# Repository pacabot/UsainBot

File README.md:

# UsainBot

Robot suiveur de ligne de l'équipe **Pacabot**, conçu pour l'épreuve **Formule 1** du
Tournoi National de Robotique Sumo (règlement v2.11, 2025).

Course de vitesse contre la montre sur circuit fermé : ligne noire de 19 mm sur bâche
blanche, rayon de virage minimum de 200 mm, lignes droites jusqu'à 6 m. Trois phases de
qualification, de difficulté croissante — Q3 piste nue, Q2 avec un cube de 100 mm à
éviter sans contact, Q1 avec en plus un virage à gauche escamoté et un mur de 100 mm de
haut placé à 150 mm à gauche de l'axe de la piste absente.

## Organisation

```
electronics/      projet KiCad — schéma, PCB, table de bibliothèques
  kicad-lib/      empreintes et modèles 3D propres au projet
firmware/         à venir : configuration STM32CubeMX du H723ZGT6, puis le code
mechanics/        sources FreeCAD du châssis, des supports et de la carte
documentation/    document d'architecture
rules/            règlement de l'épreuve
```

Les bibliothèques sont référencées en `${KIPRJMOD}/kicad-lib/…` : le dépôt se clone et
s'ouvre tel quel, sans chemin absolu ni variable d'environnement à déclarer.

Le projet s'ouvre avec **KiCad 10.0** stable. Le routage se fait avec un fork 10.99
(autorouteur) qui enregistre la carte dans un format que 10.0 refuse : après chaque
enregistrement depuis le fork, ramener la carte au format 10.0 avant de commiter.

```sh
cd electronics && python3 tools/to_kicad10.py UsainBot.kicad_pcb
```

## Architecture

Le document de conception — choix du microcontrôleur, schémas blocs, implantation,
élévations, affectation des broches, nomenclature JLCPCB et revue de conception en
trente-sept points — est ici (rédigé avant le passage au LQFP144 et au BPV10NF : le
schéma `electronics/UsainBot.pdf` fait foi là où ils divergent) :

**[`documentation/architecture-usainbot.html`](documentation/architecture-usainbot.html)**

| Fonction | Choix | JLCPCB |
|---|---|---|
| Microcontrôleur | STM32H723ZGT6, Cortex-M7 550 MHz, LQFP144 | `C730146` |
| Capteur de ligne | 12 × ITR8307/S17, pas 10 mm, émetteurs pulsés | `C81632` |
| Télémétrie | 3 × OPV302 + BPV10NF, détection synchrone | pose manuelle |
| Inertie | LSM6DSO, 6 axes, SPI | `C2655100` |
| Puissance moteurs | 2 × DRV8874, 6 A crête, retour de courant | `C1855818` |
| Motorisation | 2 × Faulhaber 1524T006SR + codeur IE2-1024 + réducteur 15/10 3,33:1 | hors carte |
| Charge | BQ25887, 2S élévateur depuis USB-C, équilibrage | `C2761614` |
| Alimentation | Pack 2S commun sur AMASS MR30, bus 5,0–7,3 V, buck 3,3 V | `C3200405` |
| Turbine | EDF 27 mm, ESC EMAX Bullet 12A monté debout | hors carte |

## Géométrie

La garde au sol vaut `rayon de roue − hauteur de l'axe moteur au-dessus du dessous de
carte`. Les roues JSumo JS4311 font 43 mm ; l'équerre usinée et trois cales de 1,6 mm
tirées du panneau de la carte placent l'axe à 16,50 mm au-dessus du dessous de carte, ce
qui donne **5,00 mm de garde**, dans la plage utile de l'ITR8307. Toutes les cotes
dérivent de `electronics/kicad-lib/faulhaber_geom.py` (détail dans
`electronics/kicad-lib/README.md`).

## Points ouverts

- **Pack commun 2S.** Cellules, capacité, chimie et protection générale à arrêter ; la
  recharge BQ25887 reste inhibée jusqu'à configuration et validation du firmware.
- **Montage de l'ESC.** L'empreinte `EMAX_Bullet_12A_Vertical_3Pin_PROTOTYPE` est tirée
  de photographies : mesurer pads, épaisseur et continuités de masse sur l'ESC réel avant
  fabrication.

- **Départ par télémètre.** Le chapitre 2 du règlement énumère trois moyens de départ —
  interrupteur, bouton poussoir, jack — et cette liste se lit comme limitative. Question à
  poser aux organisateurs ; un bouton physique conforme est conservé en secours.
- **Porteuse de la télémétrie.** À choisir hors de la bande de scintillement des
  éclairages et à l'écart des 38 kHz des barrières de chronométrage, avec un codage propre
  au robot pour la réjection par corrélation. À caler sur plaque d'essai. Rester à 12 mA :
  monter en fréquence pour débloquer les 48 mA de l'OPV302 ne change pas la puissance
  moyenne, donc pas la portée — les deux régimes donnent 1,26 mW. Le seul levier de portée
  est la surface du récepteur.
- **Inclinaison des diodes.** 4° vers le haut, soudées à plat sur la carte. Le rayon bas du
  faisceau monte alors de 35 mm par mètre et n'atteint jamais la bâche, mais le centre passe
  au-dessus d'un cube de 100 mm au-delà d'environ un mètre.
- **Approvisionnement.** OPV302 et BPV10NF ne sont probablement pas dans la bibliothèque
  JLCPCB : pose manuelle des six composants de la languette à prévoir.
- **Poussée de la turbine.** À mesurer sous 6,4 V et non sous les 8,4 V pour lesquels les
  ensembles ESC et brushless du commerce sont calibrés.

## Contenu tiers

- `rules/Reglement-Formule-1-v2.11.pdf` — règlement rédigé par Frédéric Giamarchi et
  Jean-Roch Vaillé pour le Tournoi National de Robotique Sumo. Publié sur
  [robot-sumo.fr](https://robot-sumo.fr), reproduit ici pour le confort de travail de
  l'équipe. Tous droits réservés à leurs auteurs.
- `electronics/kicad-lib/3d/vendor/*.stp` — modèles Faulhaber du moteur 1524 et du
  réducteur 15/10. Provenance dans `electronics/kicad-lib/3d/vendor/README.md`.

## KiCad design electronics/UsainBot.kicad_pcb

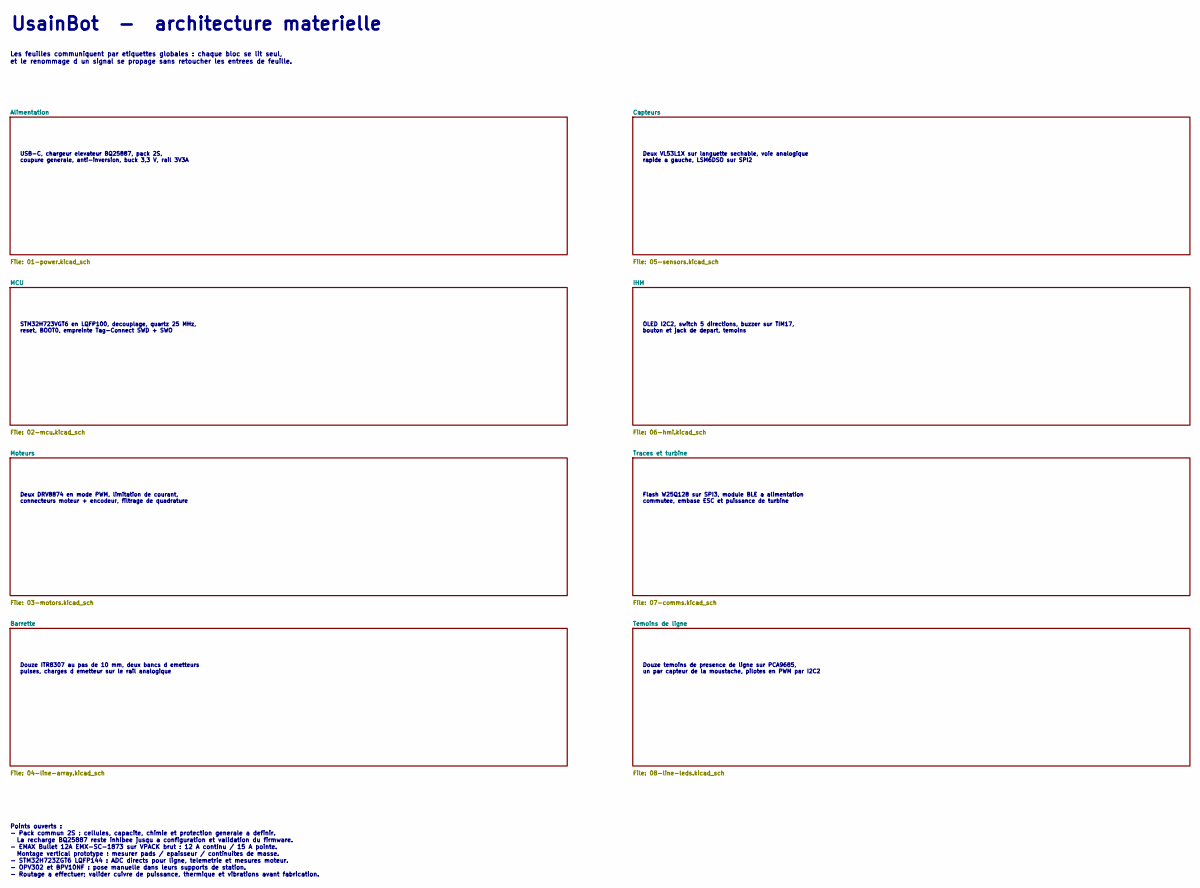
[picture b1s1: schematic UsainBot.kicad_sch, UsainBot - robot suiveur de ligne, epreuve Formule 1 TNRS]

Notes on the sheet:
USB-C, chargeur elevateur BQ25887, pack 2S, coupure generale, anti-inversion, buck 3,3 V, rail 3V3A
Flash W25Q128 sur SPI3, module BLE a alimentation commutee, embase ESC et puissance de turbine
Douze ITR8307 au pas de 10 mm, deux bancs d emetteurs pulses, charges d emetteur sur le rail analogique
Douze temoins de presence de ligne sur PCA9685, un par capteur de la moustache, pilotes en PWM par I2C2
Les feuilles communiquent par etiquettes globales : chaque bloc se lit seul, et le renommage d un signal se propage sans retoucher les entrees de feuille.
Deux VL53L1X sur languette sechable, voie analogique rapide a gauche, LSM6DSO sur SPI2
OLED I2C2, switch 5 directions, buzzer sur TIM17, bouton et jack de depart, temoins
Deux DRV8874 en mode PWM, limitation de courant, connecteurs moteur + encodeur, filtrage de quadrature
STM32H723VGT6 en LQFP100, decouplage, quartz 25 MHz, reset, BOOT0, empreinte Tag-Connect SWD + SWO
Points ouverts : - Pack commun 2S : cellules, capacite, chimie et protection generale a definir. La recharge BQ25887 reste inhibee jusqu a configuration et validation du firmware. - EMAX Bullet 12A EMX-SC-1873 sur VPACK brut : 12 A continu / 15 A pointe. Montage vertical prototype : mesurer pads / 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
UsainBot - architecture materielle

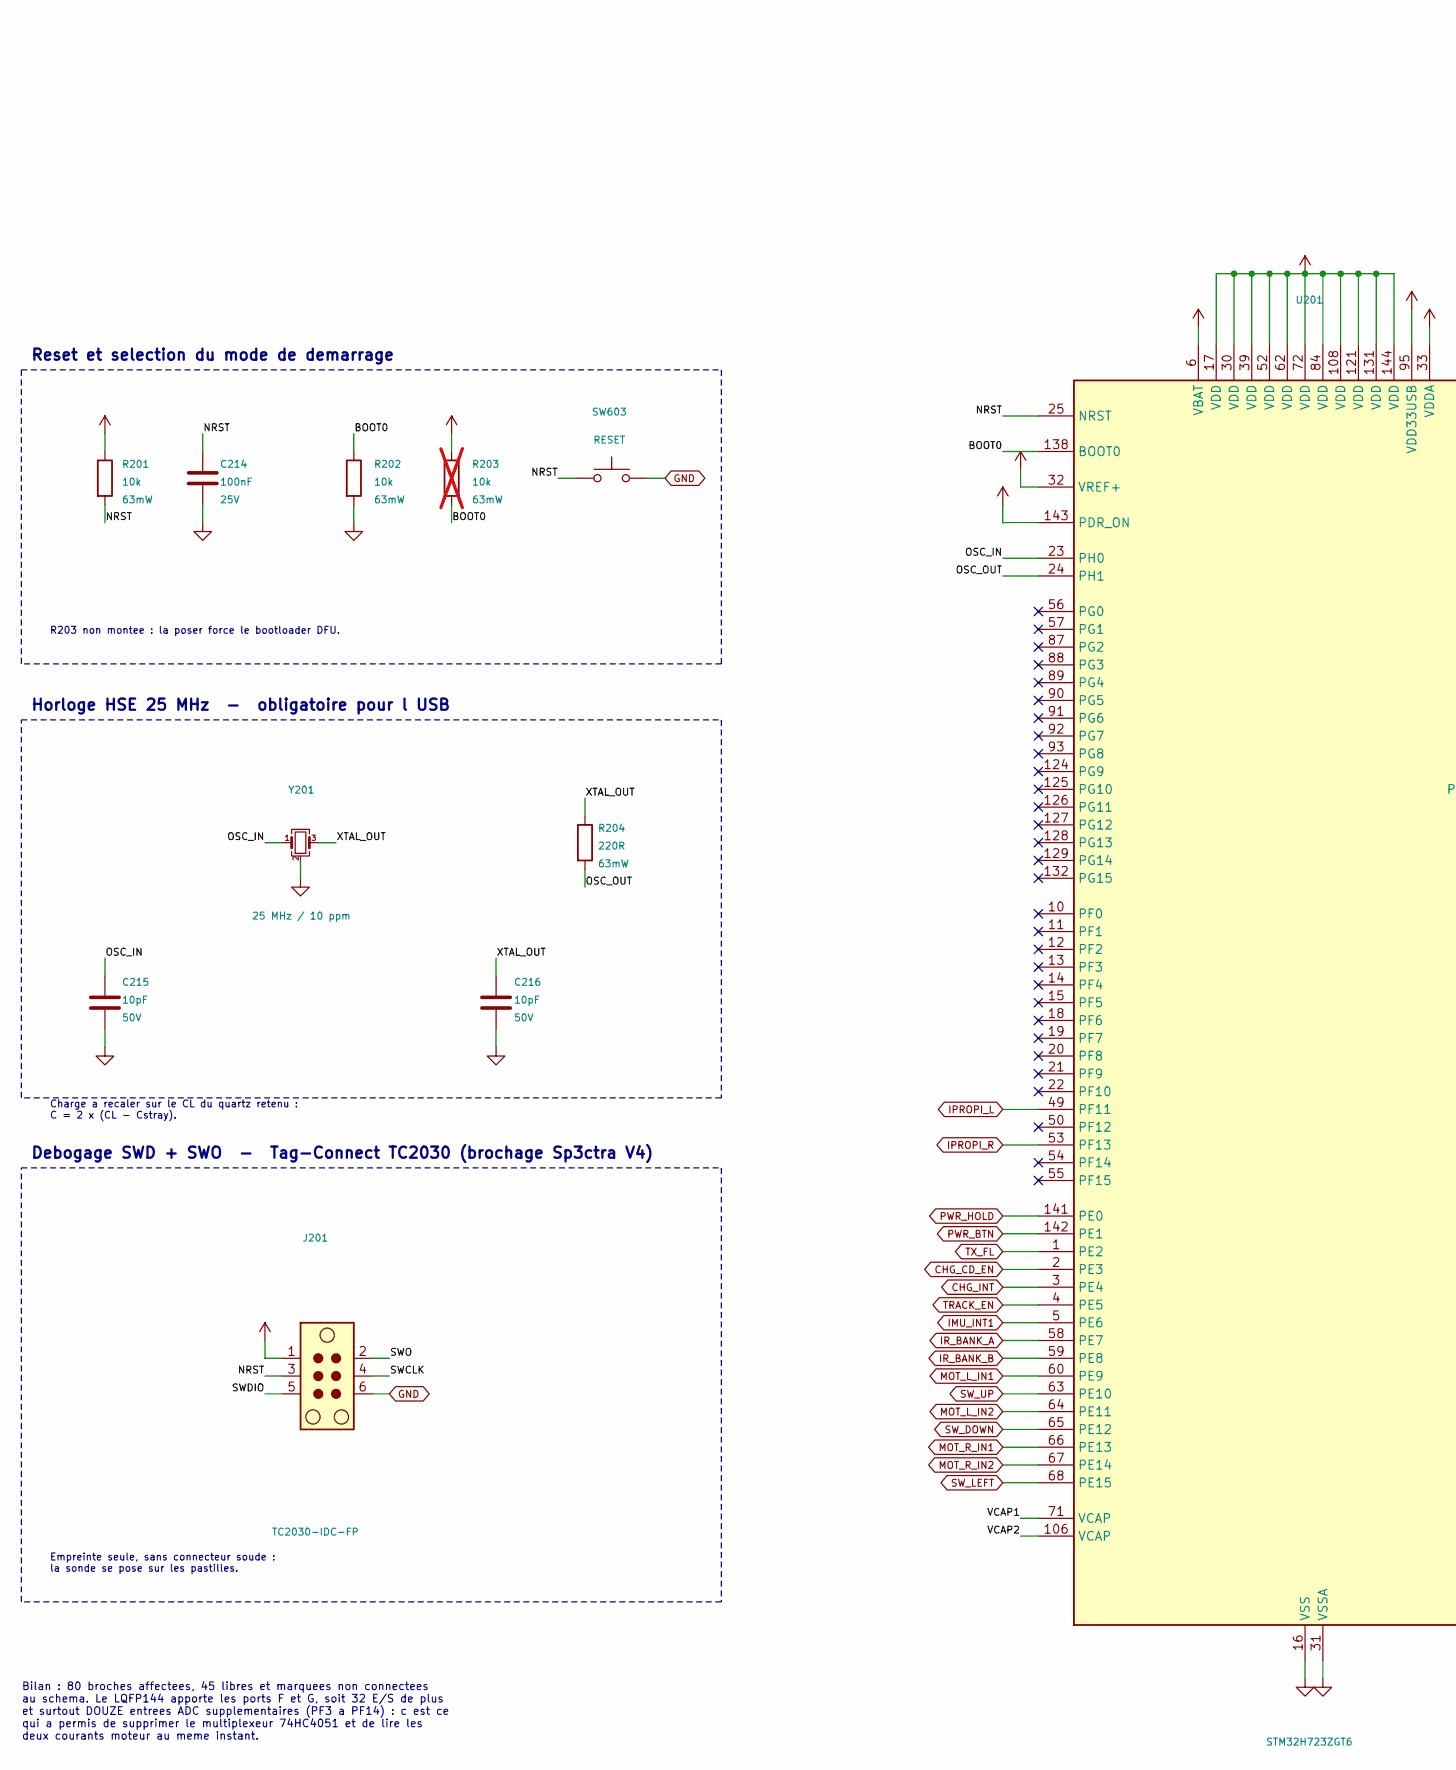
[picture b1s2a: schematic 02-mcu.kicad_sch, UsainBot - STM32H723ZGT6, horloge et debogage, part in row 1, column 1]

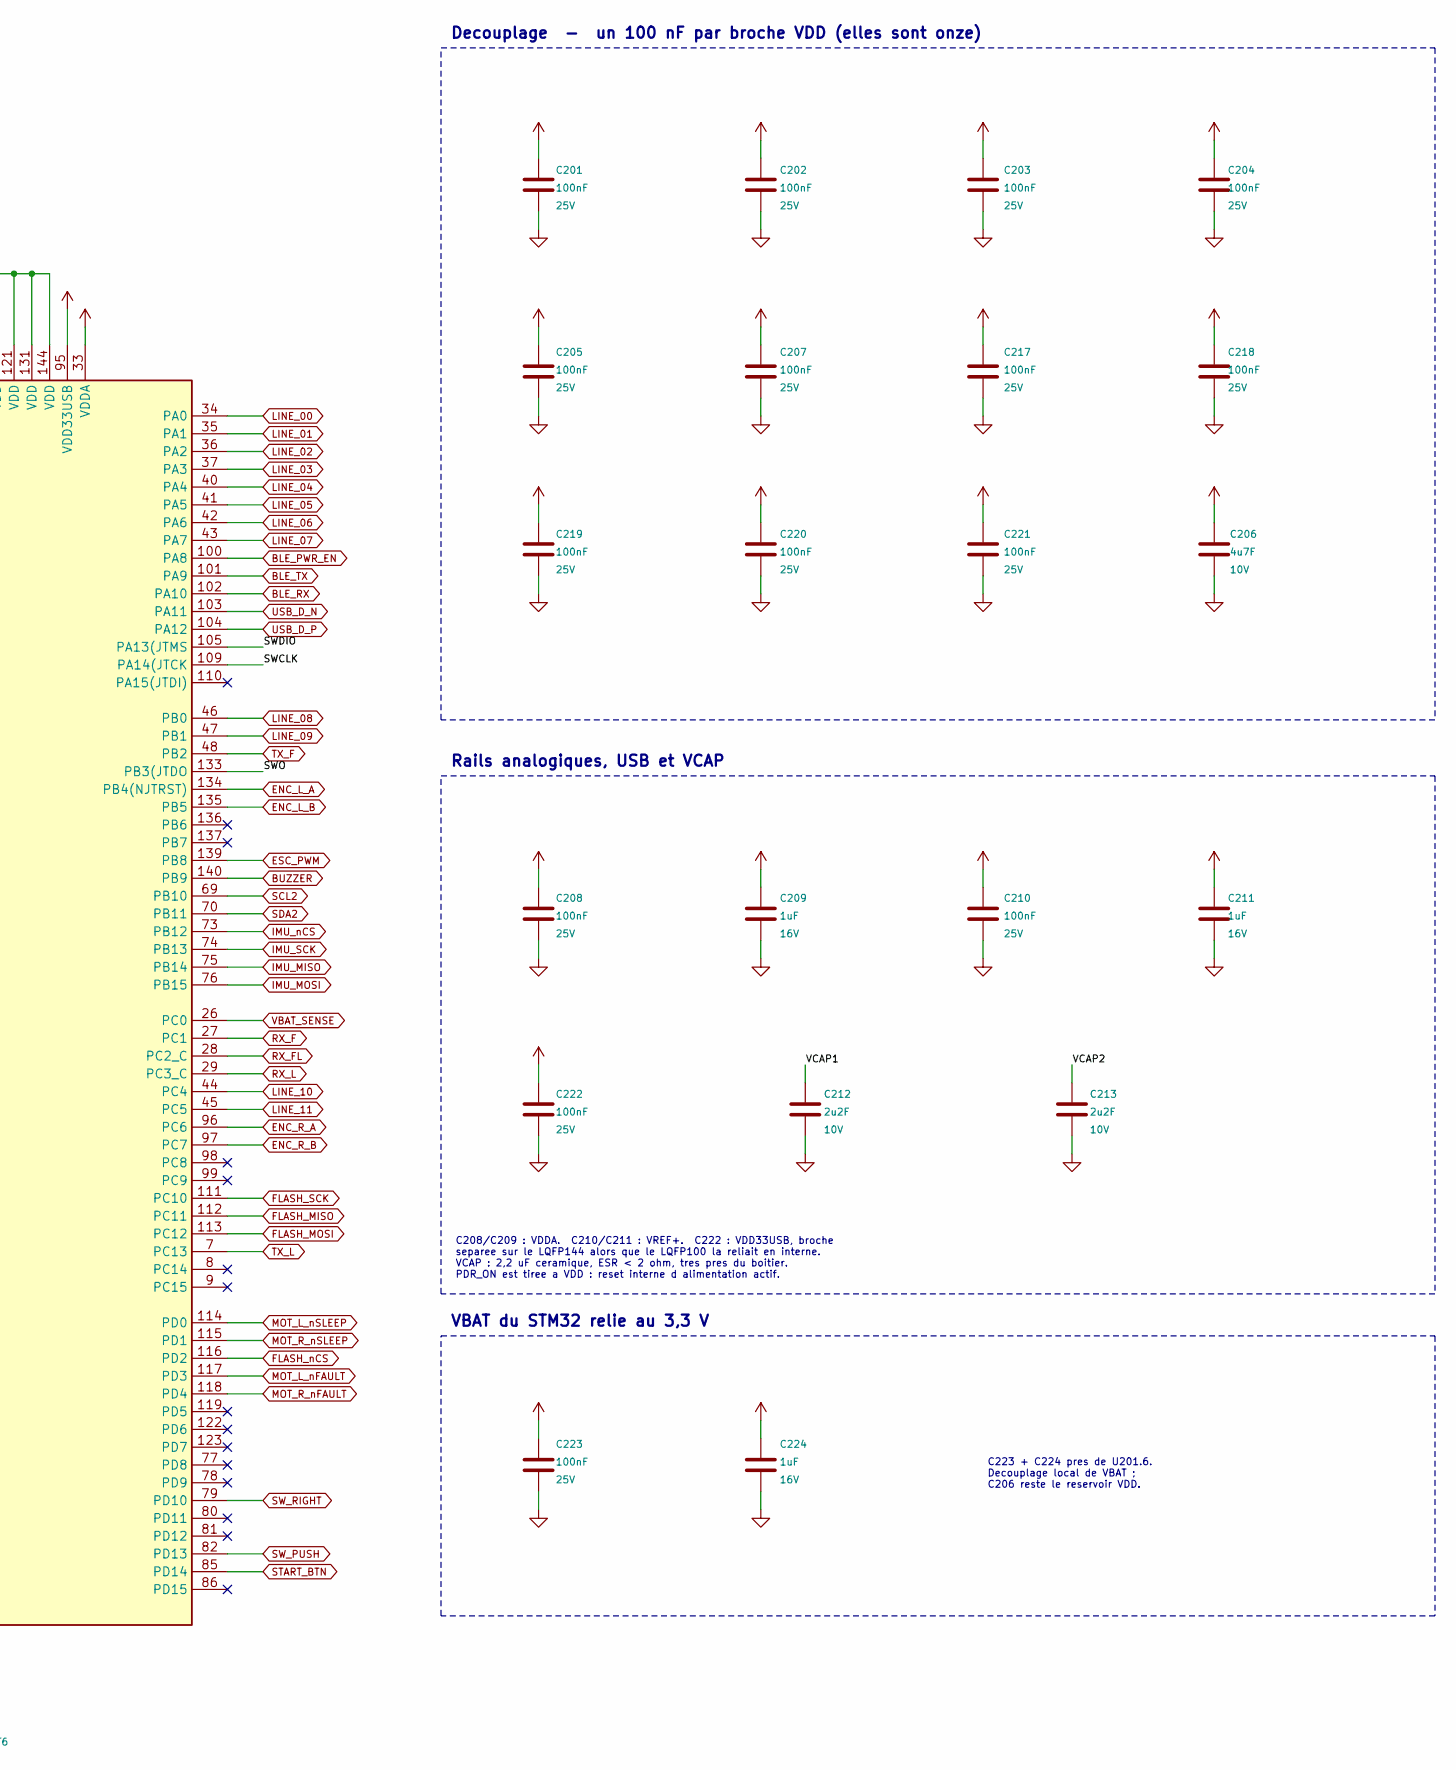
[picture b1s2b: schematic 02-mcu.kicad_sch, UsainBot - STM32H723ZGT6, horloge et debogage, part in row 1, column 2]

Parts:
C201, C202, C203, C204, C205, C207, C208, C210, C214, C217, C218, C219, C220, C221, C222, C223: 100nF; C_0402_1005Metric; Voltage 25V
C206: 4u7F; C_0805_2012Metric; Voltage 10V
C209, C211, C224: 1uF; C_0402_1005Metric; Voltage 16V
C212, C213: 2u2F; C_0805_2012Metric; Voltage 10V
C215, C216: 10pF; C_0402_1005Metric; Voltage 50V
J201: TC2030-IDC-FP; Tag-Connect_TC2030-IDC-FP_2x03_P1.27mm_Vertical
R201, R202: 10k; R_0402_1005Metric
R203: 10k; R_0402_1005Metric; not fitted
R204: 220R; R_0402_1005Metric
SW603: RESET; SW_SPST_B3U-1000P
U201: STM32H723ZGT6; LQFP-144_20x20mm_P0.5mm; LCSC C730146
Y201: 25 MHz / 10 ppm; Crystal_SMD_3225-4Pin_3.2x2.5mm

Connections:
/MCU/BOOT0: R202.1, R203.2, U201.138 (BOOT0)
/MCU/NRST: C214.1, J201.3, R201.2, SW603.1, U201.25 (NRST)
/MCU/OSC_IN: C215.1, U201.23 (PH0), Y201.1
/MCU/OSC_OUT: R204.2, U201.24 (PH1)
/MCU/SWCLK: J201.4, U201.109 (PA14(JTCK)
/MCU/SWDIO: J201.5, U201.105 (PA13(JTMS)
/MCU/SWO: J201.2, U201.133 (PB3(JTDO)
/MCU/VCAP1: C212.1, U201.71 (VCAP)
/MCU/VCAP2: C213.1, U201.106 (VCAP)
/MCU/XTAL_OUT: C216.1, R204.1, Y201.3
BLE_PWR_EN: U201.100 (PA8); also elsewhere on the board
BLE_RX: U201.102 (PA10); also elsewhere on the board
BLE_TX: U201.101 (PA9); also elsewhere on the board
BUZZER: U201.140 (PB9); also elsewhere on the board
CHG_CD_EN: U201.2 (PE3); also elsewhere on the board
CHG_INT: U201.3 (PE4); also elsewhere on the board
ENC_L_A: U201.134 (PB4(NJTRST)); also elsewhere on the board
ENC_L_B: U201.135 (PB5); also elsewhere on the board
ENC_R_A: U201.96 (PC6); also elsewhere on the board
ENC_R_B: U201.97 (PC7); also elsewhere on the board
ESC_PWM: U201.139 (PB8); also elsewhere on the board
FLASH_MISO: U201.112 (PC11); also elsewhere on the board
FLASH_MOSI: U201.113 (PC12); also elsewhere on the board
FLASH_SCK: U201.111 (PC10); also elsewhere on the board
FLASH_nCS: U201.116 (PD2); also elsewhere on the board
IMU_INT1: U201.5 (PE6); also elsewhere on the board
IMU_MISO: U201.75 (PB14); also elsewhere on the board
IMU_MOSI: U201.76 (PB15); also elsewhere on the board
IMU_SCK: U201.74 (PB13); also elsewhere on the board
IMU_nCS: U201.73 (PB12); also elsewhere on the board
IPROPI_L: U201.49 (PF11); also elsewhere on the board
IPROPI_R: U201.53 (PF13); also elsewhere on the board
IR_BANK_A: U201.58 (PE7); also elsewhere on the board
IR_BANK_B: U201.59 (PE8); also elsewhere on the board
LINE_00: U201.34 (PA0); also elsewhere on the board
LINE_01: U201.35 (PA1); also elsewhere on the board
LINE_02: U201.36 (PA2); also elsewhere on the board
LINE_03: U201.37 (PA3); also elsewhere on the board
LINE_04: U201.40 (PA4); also elsewhere on the board
LINE_05: U201.41 (PA5); also elsewhere on the board
LINE_06: U201.42 (PA6); also elsewhere on the board
LINE_07: U201.43 (PA7); also elsewhere on the board
LINE_08: U201.46 (PB0); also elsewhere on the board
LINE_09: U201.47 (PB1); also elsewhere on the board
LINE_10: U201.44 (PC4); also elsewhere on the board
LINE_11: U201.45 (PC5); also elsewhere on the board
MOT_L_IN1: U201.60 (PE9); also elsewhere on the board
MOT_L_IN2: U201.64 (PE11); also elsewhere on the board
MOT_L_nFAULT: U201.117 (PD3); also elsewhere on the board
MOT_L_nSLEEP: U201.114 (PD0); also elsewhere on the board
MOT_R_IN1: U201.66 (PE13); also elsewhere on the board
MOT_R_IN2: U201.67 (PE14); also elsewhere on the board
MOT_R_nFAULT: U201.118 (PD4); also elsewhere on the board
MOT_R_nSLEEP: U201.115 (PD1); also elsewhere on the board
PWR_BTN: U201.142 (PE1); also elsewhere on the board
PWR_HOLD: U201.141 (PE0); also elsewhere on the board
RX_F: U201.27 (PC1); also elsewhere on the board
RX_FL: U201.28 (PC2_C); also elsewhere on the board
RX_L: U201.29 (PC3_C); also elsewhere on the board
SCL2: U201.69 (PB10); also elsewhere on the board
SDA2: U201.70 (PB11); also elsewhere on the board
START_BTN: U201.85 (PD14); also elsewhere on the board
SW_DOWN: U201.65 (PE12); also elsewhere on the board
SW_LEFT: U201.68 (PE15); also elsewhere on the board
SW_PUSH: U201.82 (PD13); also elsewhere on the board
SW_RIGHT: U201.79 (PD10); also elsewhere on the board
SW_UP: U201.63 (PE10); also elsewhere on the board
TRACK_EN: U201.4 (PE5); also elsewhere on the board
TX_F: U201.48 (PB2); also elsewhere on the board
TX_FL: U201.1 (PE2); also elsewhere on the board
TX_L: U201.7 (PC13); also elsewhere on the board
USB_D_N: U201.103 (PA11); also elsewhere on the board
USB_D_P: U201.104 (PA12); also elsewhere on the board
VBAT_SENSE: U201.26 (PC0); also elsewhere on the board

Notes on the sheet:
C223 + C224 pres de U201.6. Decouplage local de VBAT ; C206 reste le reservoir VDD.
Reset et selection du mode de demarrage
Bilan : 80 broches affectees, 45 libres et marquees non connectees au schema. Le LQFP144 apporte les ports F et G, soit 32 E/S de plus et surtout DOUZE entrees ADC supplementaires (PF3 a PF14) : c est ce qui a permis de supprimer le multiplexeur 74HC4051 et de lire les deux courants moteur au meme 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
Debogage SWD + SWO - Tag-Connect TC2030 (brochage Sp3ctra V4)
Rails analogiques, USB et VCAP
C208/C209 : VDDA. C210/C211 : VREF+. C222 : VDD33USB, broche separee sur le LQFP144 alors que le LQFP100 la reliait en interne. VCAP : 2,2 uF ceramique, ESR < 2 ohm, tres pres du boitier. PDR_ON est tiree a VDD : reset interne d alimentation actif.
Charge a recaler sur le CL du quartz retenu : C = 2 x (CL - Cstray).
R203 non montee : la poser force le bootloader DFU.
Horloge HSE 25 MHz - obligatoire pour l USB
Decouplage - un 100 nF par broche VDD (elles sont onze)
Empreinte seule, sans connecteur soude : la sonde se pose sur les pastilles.
VBAT du STM32 relie au 3,3 V

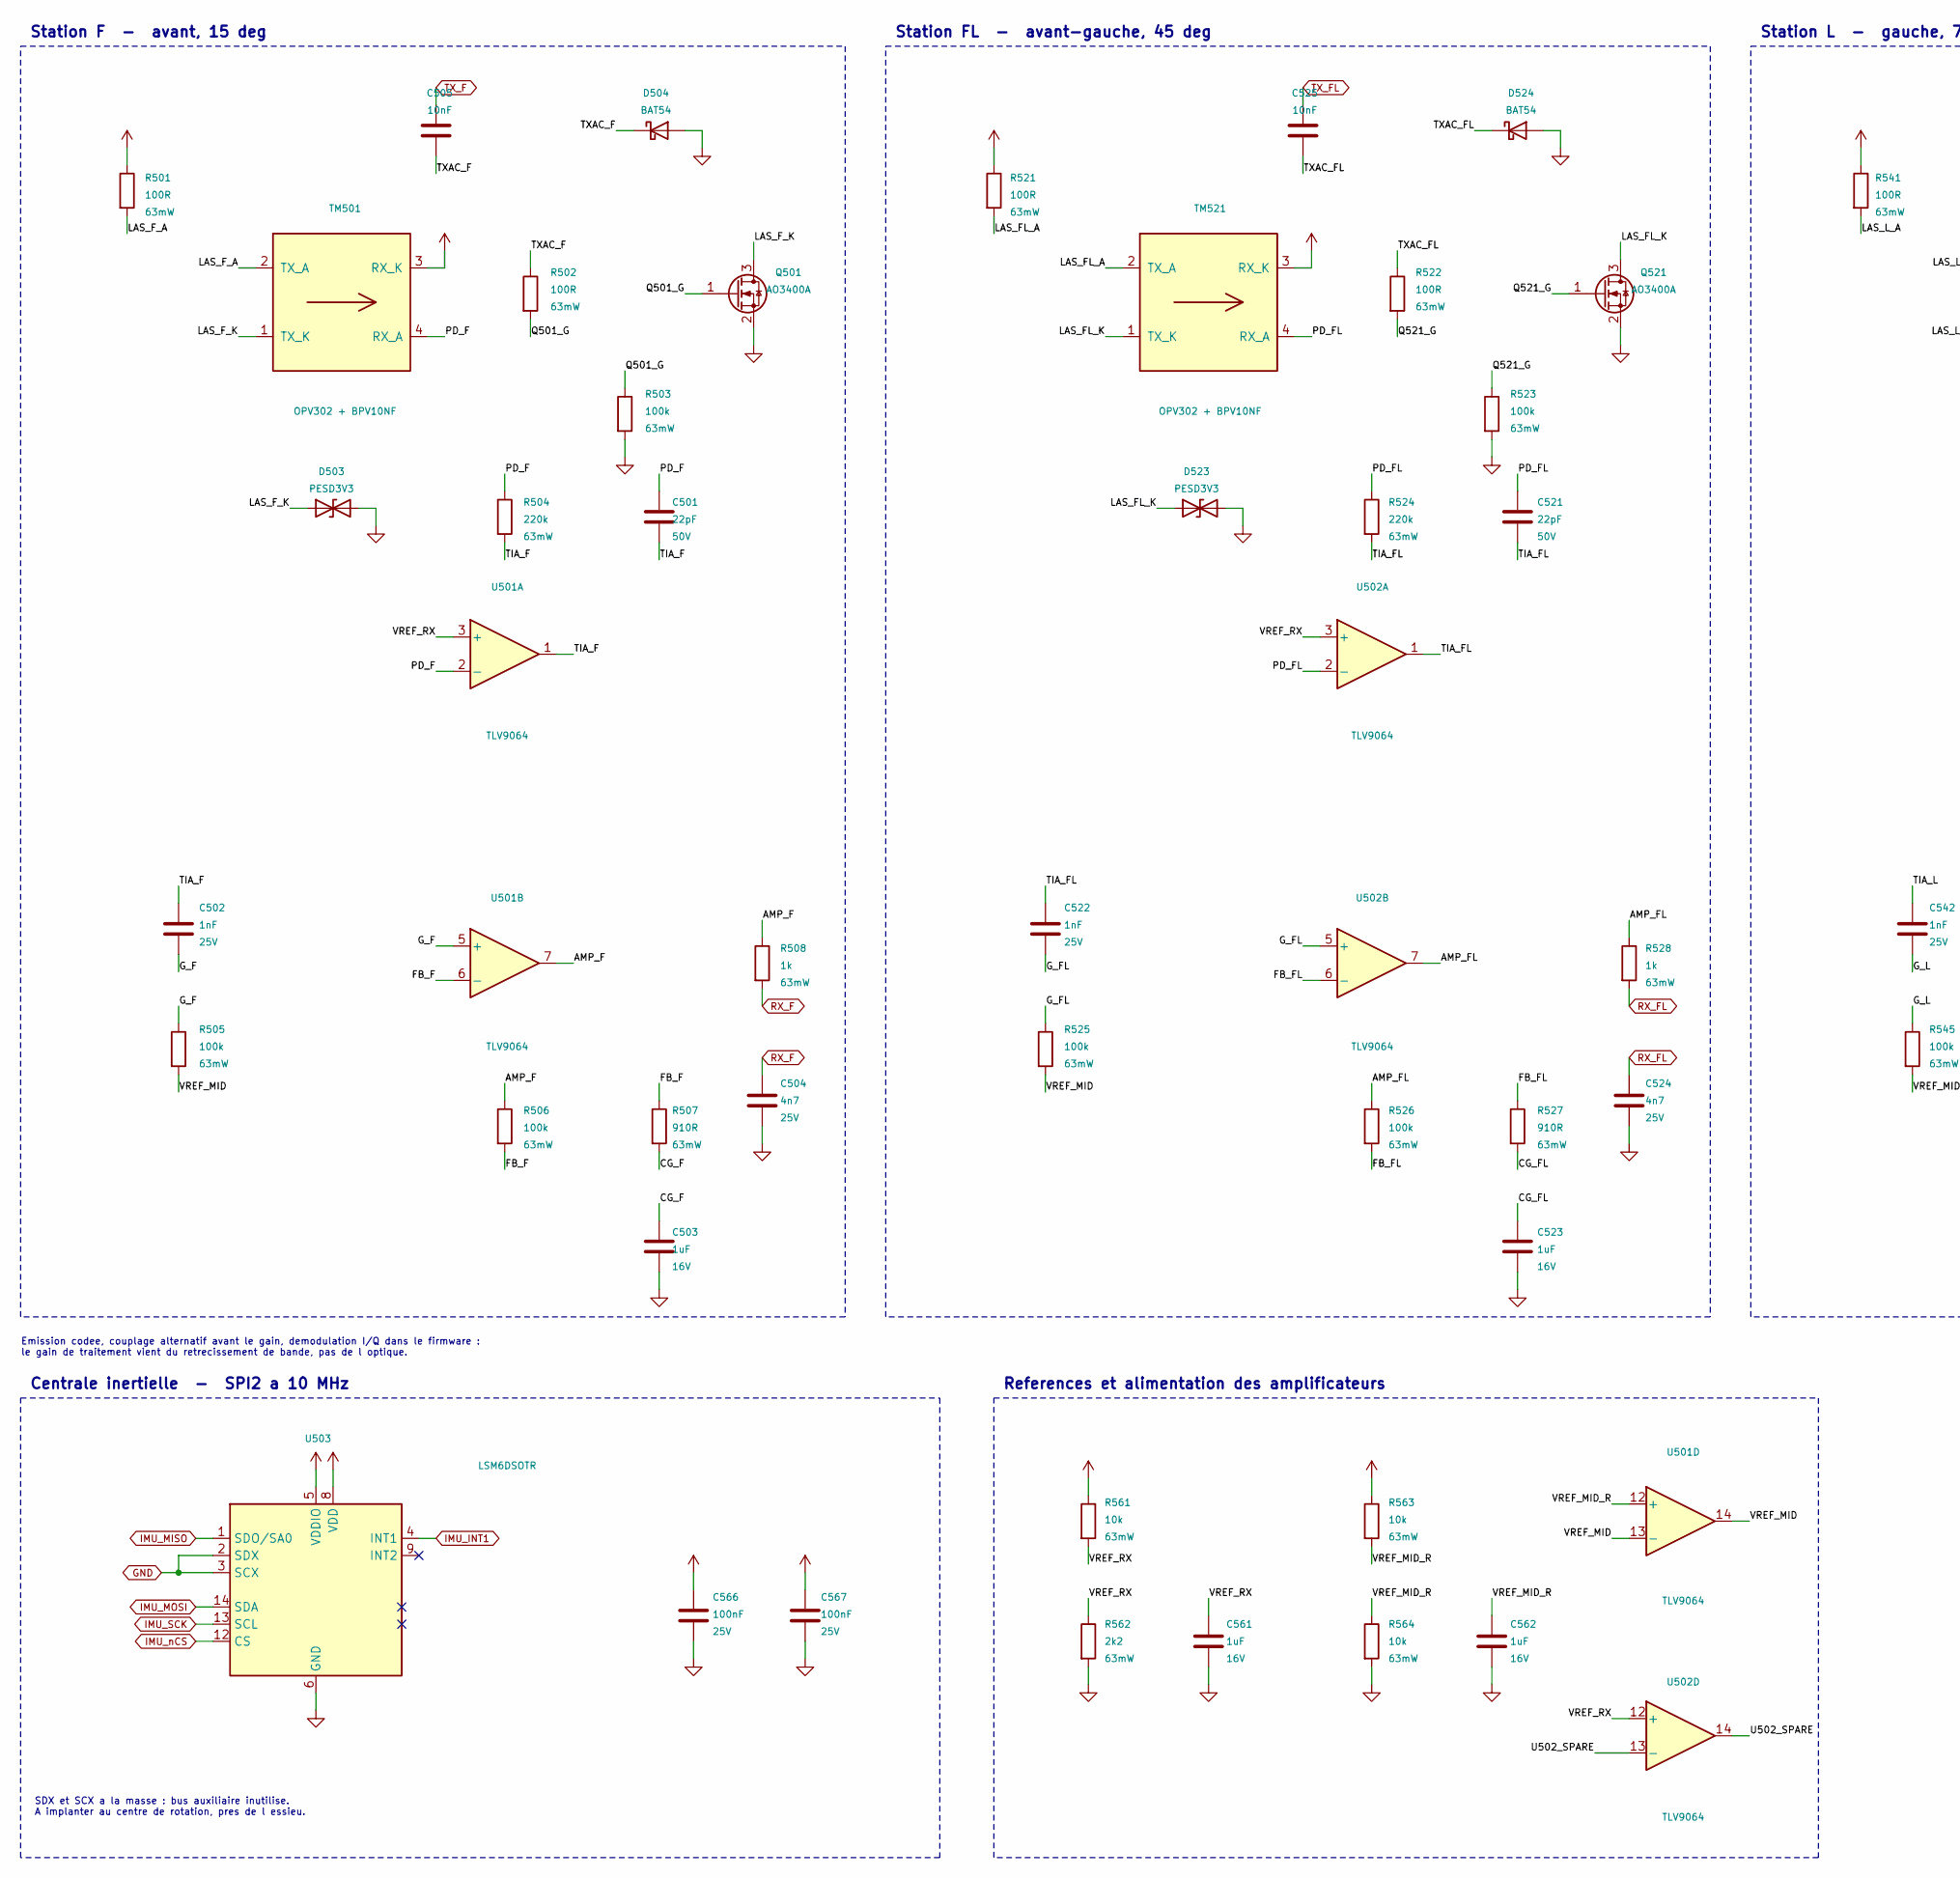
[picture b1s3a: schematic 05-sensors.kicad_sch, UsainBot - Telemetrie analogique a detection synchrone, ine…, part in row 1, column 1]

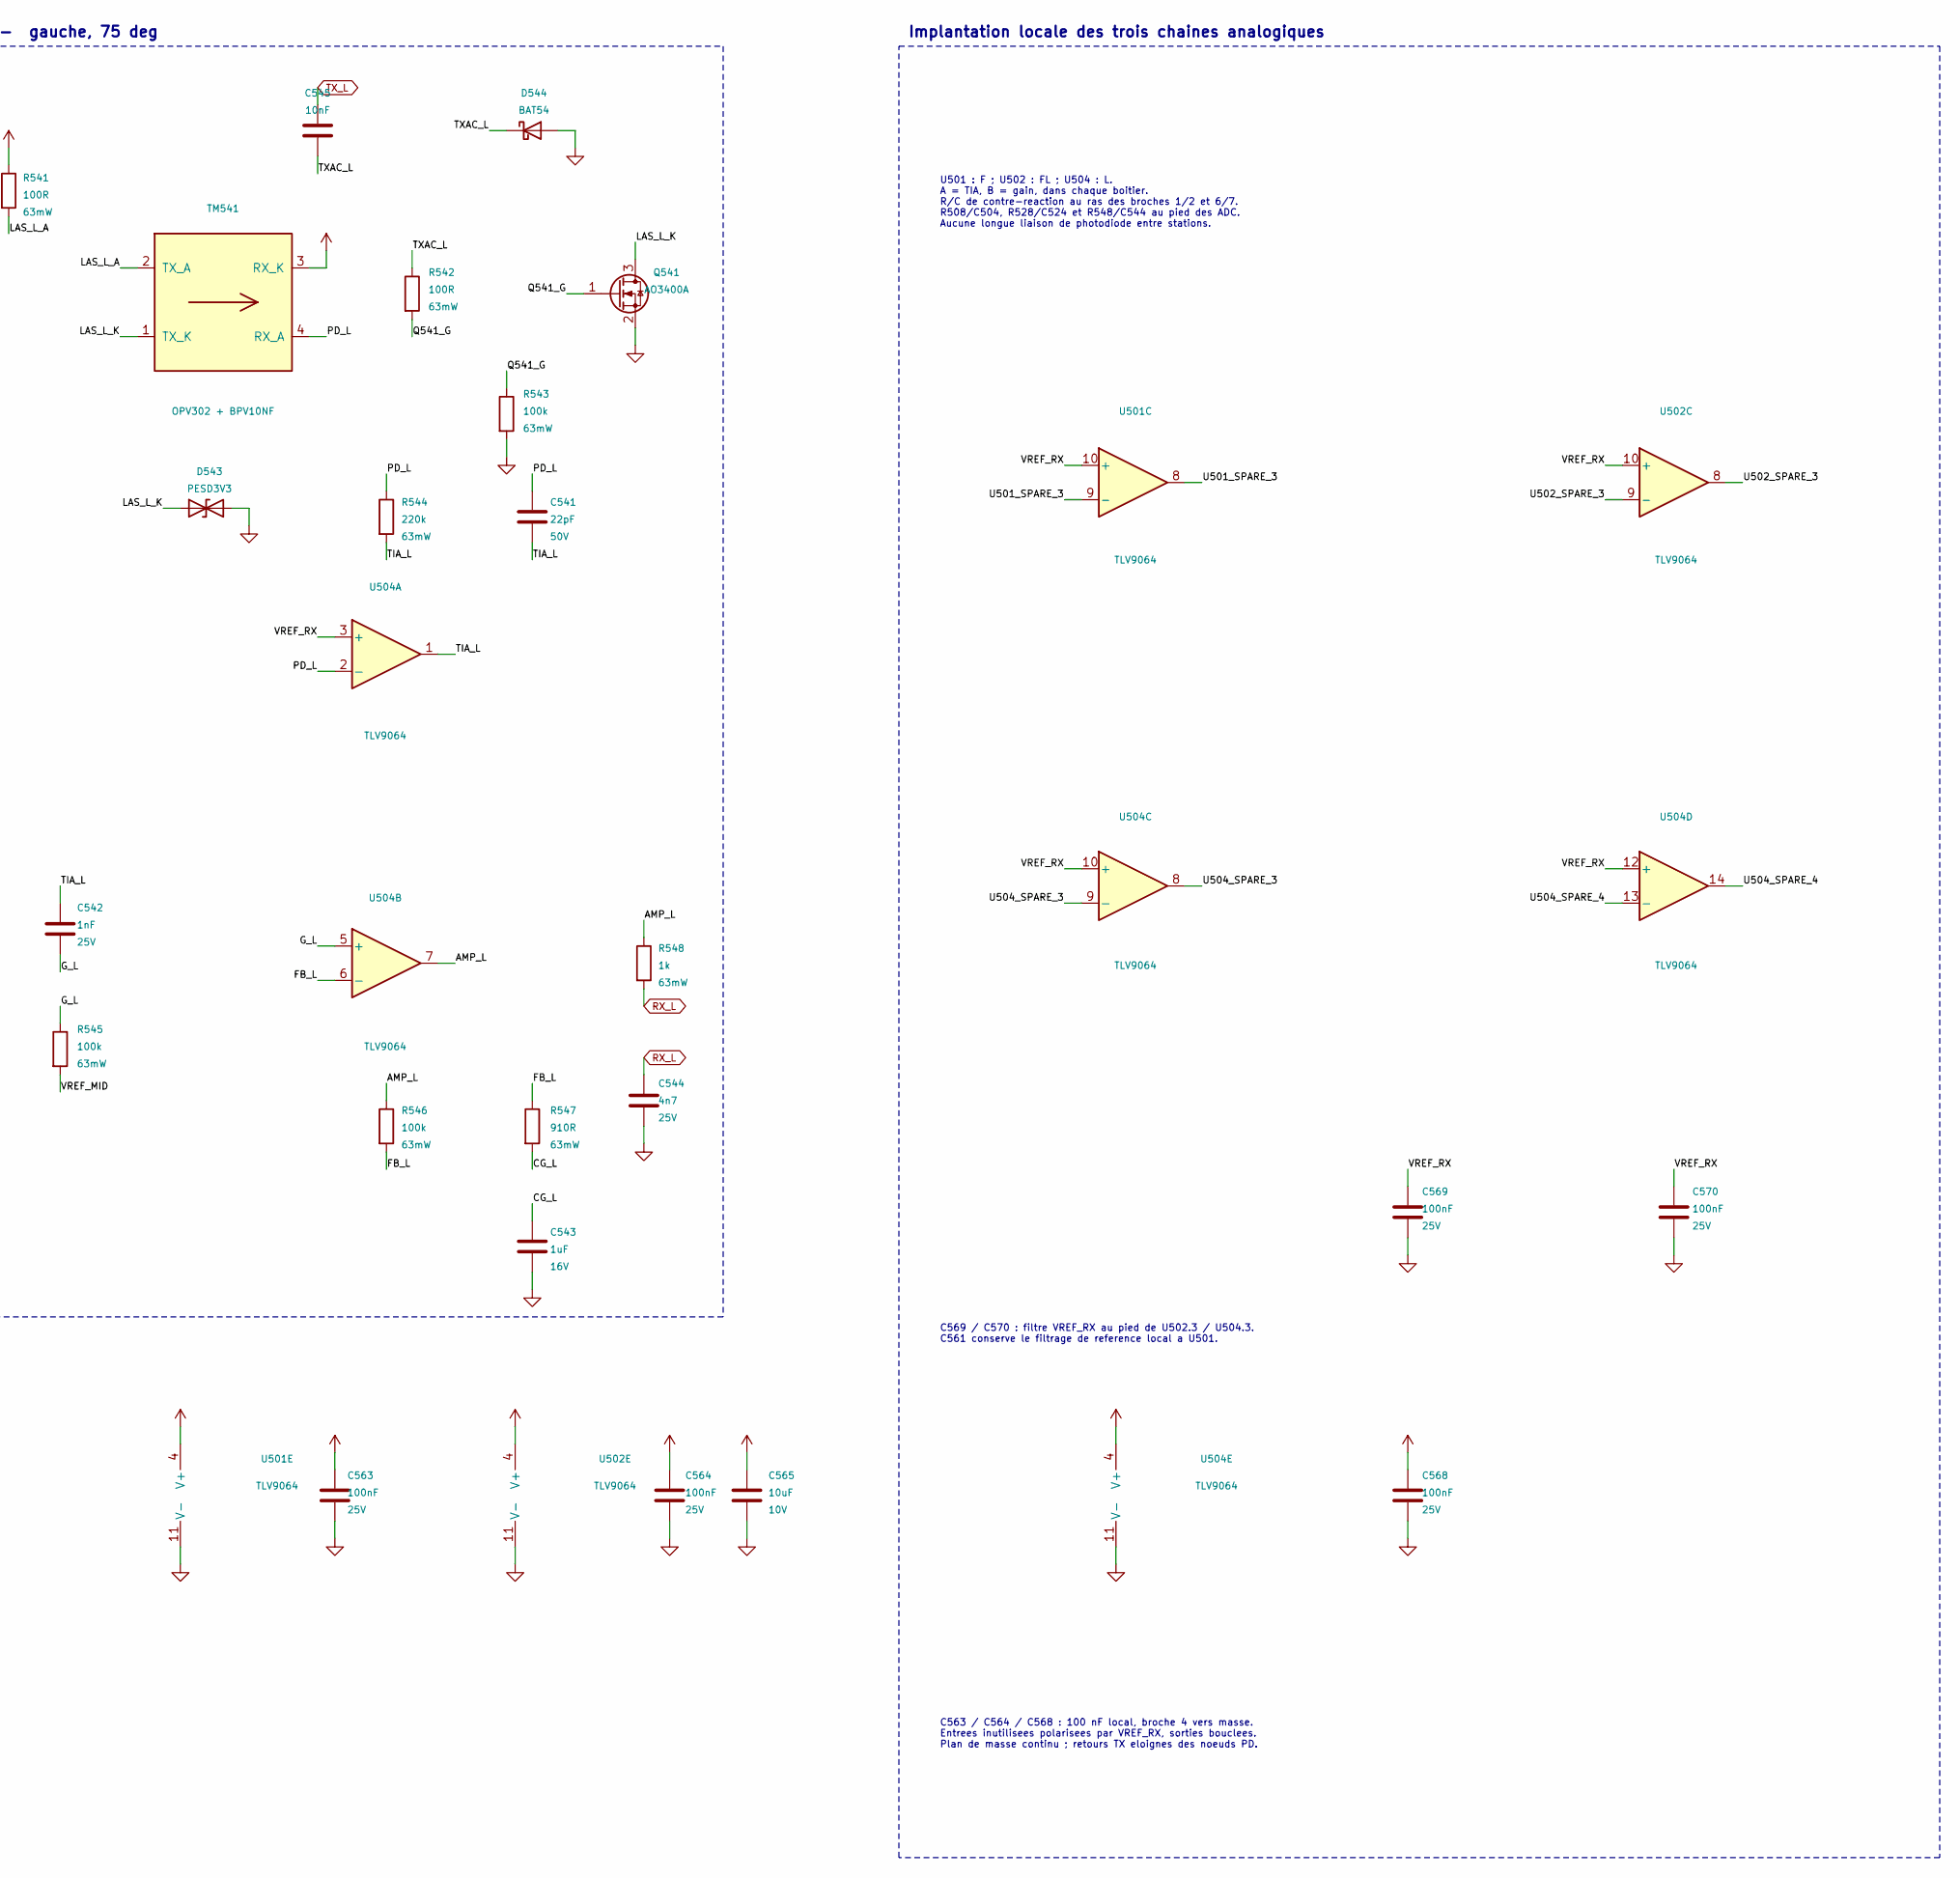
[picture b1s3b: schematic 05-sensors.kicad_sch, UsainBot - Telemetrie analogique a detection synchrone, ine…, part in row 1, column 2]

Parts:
C501, C521, C541: 22pF; C_0402_1005Metric; Voltage 50V
C502, C522, C542: 1nF; C_0402_1005Metric; Voltage 25V
C503, C523, C543, C561, C562: 1uF; C_0402_1005Metric; Voltage 16V
C504, C524, C544: 4n7; C_0402_1005Metric; Voltage 25V
C505, C525, C545: 10nF; C_0402_1005Metric
C563, C564, C566, C567, C568, C569, C570: 100nF; C_0402_1005Metric; Voltage 25V
C565: 10uF; C_0805_2012Metric; Voltage 10V
D503, D523, D543: PESD3V3; D_SOD-323
D504, D524, D544: BAT54; D_SOD-323
Q501, Q521, Q541: AO3400A; SOT-23
R501, R502, R521, R522, R541, R542: 100R; R_0402_1005Metric
R503, R505, R506, R523, R525, R526, R543, R545, R546: 100k; R_0402_1005Metric
R504, R524, R544: 220k; R_0402_1005Metric
R507, R527, R547: 910R; R_0402_1005Metric
R508, R528, R548: 1k; R_0402_1005Metric
R561, R563, R564: 10k; R_0402_1005Metric
R562: 2k2; R_0402_1005Metric
TM501, TM521, TM541: OPV302 + BPV10NF; Telemetry_Duo_Coude
U501, U502, U504: TLV9064; TSSOP-14_4.4x5mm_P0.65mm
U503: LSM6DSOTR; LGA-14_3x2.5mm_P0.5mm_LayoutBorder3x4y; LCSC C2655100

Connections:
/Capteurs/AMP_F: R506.1, R508.1, U501.7
/Capteurs/AMP_FL: R526.1, R528.1, U502.7
/Capteurs/AMP_L: R546.1, R548.1, U504.7
/Capteurs/CG_F: C503.1, R507.2
/Capteurs/CG_FL: C523.1, R527.2
/Capteurs/CG_L: C543.1, R547.2
/Capteurs/FB_F: R506.2, R507.1, U501.6 (-)
/Capteurs/FB_FL: R526.2, R527.1, U502.6 (-)
/Capteurs/FB_L: R546.2, R547.1, U504.6 (-)
/Capteurs/G_F: C502.2, R505.1, U501.5 (+)
/Capteurs/G_FL: C522.2, R525.1, U502.5 (+)
/Capteurs/G_L: C542.2, R545.1, U504.5 (+)
/Capteurs/LAS_FL_A: R521.2, TM521.2 (TX_A)
/Capteurs/LAS_FL_K: D523.1 (A1), Q521.3 (D), TM521.1 (TX_K)
/Capteurs/LAS_F_A: R501.2, TM501.2 (TX_A)
/Capteurs/LAS_F_K: D503.1 (A1), Q501.3 (D), TM501.1 (TX_K)
/Capteurs/LAS_L_A: R541.2, TM541.2 (TX_A)
/Capteurs/LAS_L_K: D543.1 (A1), Q541.3 (D), TM541.1 (TX_K)
/Capteurs/PD_F: C501.1, R504.1, TM501.4 (RX_A), U501.2 (-)
/Capteurs/PD_FL: C521.1, R524.1, TM521.4 (RX_A), U502.2 (-)
/Capteurs/PD_L: C541.1, R544.1, TM541.4 (RX_A), U504.2 (-)
/Capteurs/Q501_G: Q501.1 (G), R502.2, R503.1
/Capteurs/Q521_G: Q521.1 (G), R522.2, R523.1
/Capteurs/Q541_G: Q541.1 (G), R542.2, R543.1
/Capteurs/TIA_F: C501.2, C502.1, R504.2, U501.1
/Capteurs/TIA_FL: C521.2, C522.1, R524.2, U502.1
/Capteurs/TIA_L: C541.2, C542.1, R544.2, U504.1
/Capteurs/TXAC_F: C505.2, D504.1 (K), R502.1
/Capteurs/TXAC_FL: C525.2, D524.1 (K), R522.1
/Capteurs/TXAC_L: C545.2, D544.1 (K), R542.1
/Capteurs/U501_SPARE_3: U501.8, U501.9 (-)
/Capteurs/U502_SPARE: U502.13 (-), U502.14
/Capteurs/U502_SPARE_3: U502.8, U502.9 (-)
/Capteurs/U504_SPARE_3: U504.8, U504.9 (-)
/Capteurs/U504_SPARE_4: U504.13 (-), U504.14
/Capteurs/VREF_MID: R505.2, R525.2, R545.2, U501.13 (-), U501.14
/Capteurs/VREF_MID_R: C562.1, R563.2, R564.1, U501.12 (+)
/Capteurs/VREF_RX: C561.1, C569.1, C570.1, R561.2, R562.1, U501.3 (+), U501.10 (+), U502.3 (+), U502.10 (+), U502.12 (+), U504.3 (+), U504.10 (+), U504.12 (+)
IMU_INT1: U503.4 (INT1); also elsewhere on the board
IMU_MISO: U503.1 (SDO/SA0); also elsewhere on the board
IMU_MOSI: U503.14 (SDA); also elsewhere on the board
IMU_SCK: U503.13 (SCL); also elsewhere on the board
IMU_nCS: U503.12 (CS); also elsewhere on the board
RX_F: C504.1, R508.2; also elsewhere on the board
RX_FL: C524.1, R528.2; also elsewhere on the board
RX_L: C544.1, R548.2; also elsewhere on the board
TX_F: C505.1; also elsewhere on the board
TX_FL: C525.1; also elsewhere on the board
TX_L: C545.1; also elsewhere on the board

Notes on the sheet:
Station F - avant, 15 deg
Centrale inertielle - SPI2 a 10 MHz
Station L - gauche, 75 deg
Implantation locale des trois chaines analogiques
U501 : F ; U502 : FL ; U504 : L. A = TIA, B = gain, dans chaque boitier. R/C de contre-reaction au ras des broches 1/2 et 6/7. R508/C504, R528/C524 et R548/C544 au pied des ADC. Aucune longue liaison de photodiode entre stations.
Station FL - avant-gauche, 45 deg
C569 / C570 : filtre VREF_RX au pied de U502.3 / U504.3. C561 conserve le filtrage de reference local a U501.
References et alimentation des amplificateurs
Emission codee, couplage alternatif avant le gain, demodulation I/Q dans le firmware : le gain de traitement vient du retrecissement de bande, pas de l optique.
SDX et SCX a la masse : bus auxiliaire inutilise. A implanter au centre de rotation, pres de l essieu.
C563 / C564 / C568 : 100 nF local, broche 4 vers masse. Entrees inutilisees polarisees par VREF_RX, sorties bouclees. Plan de masse continu ; retours TX eloignes des noeuds PD.
